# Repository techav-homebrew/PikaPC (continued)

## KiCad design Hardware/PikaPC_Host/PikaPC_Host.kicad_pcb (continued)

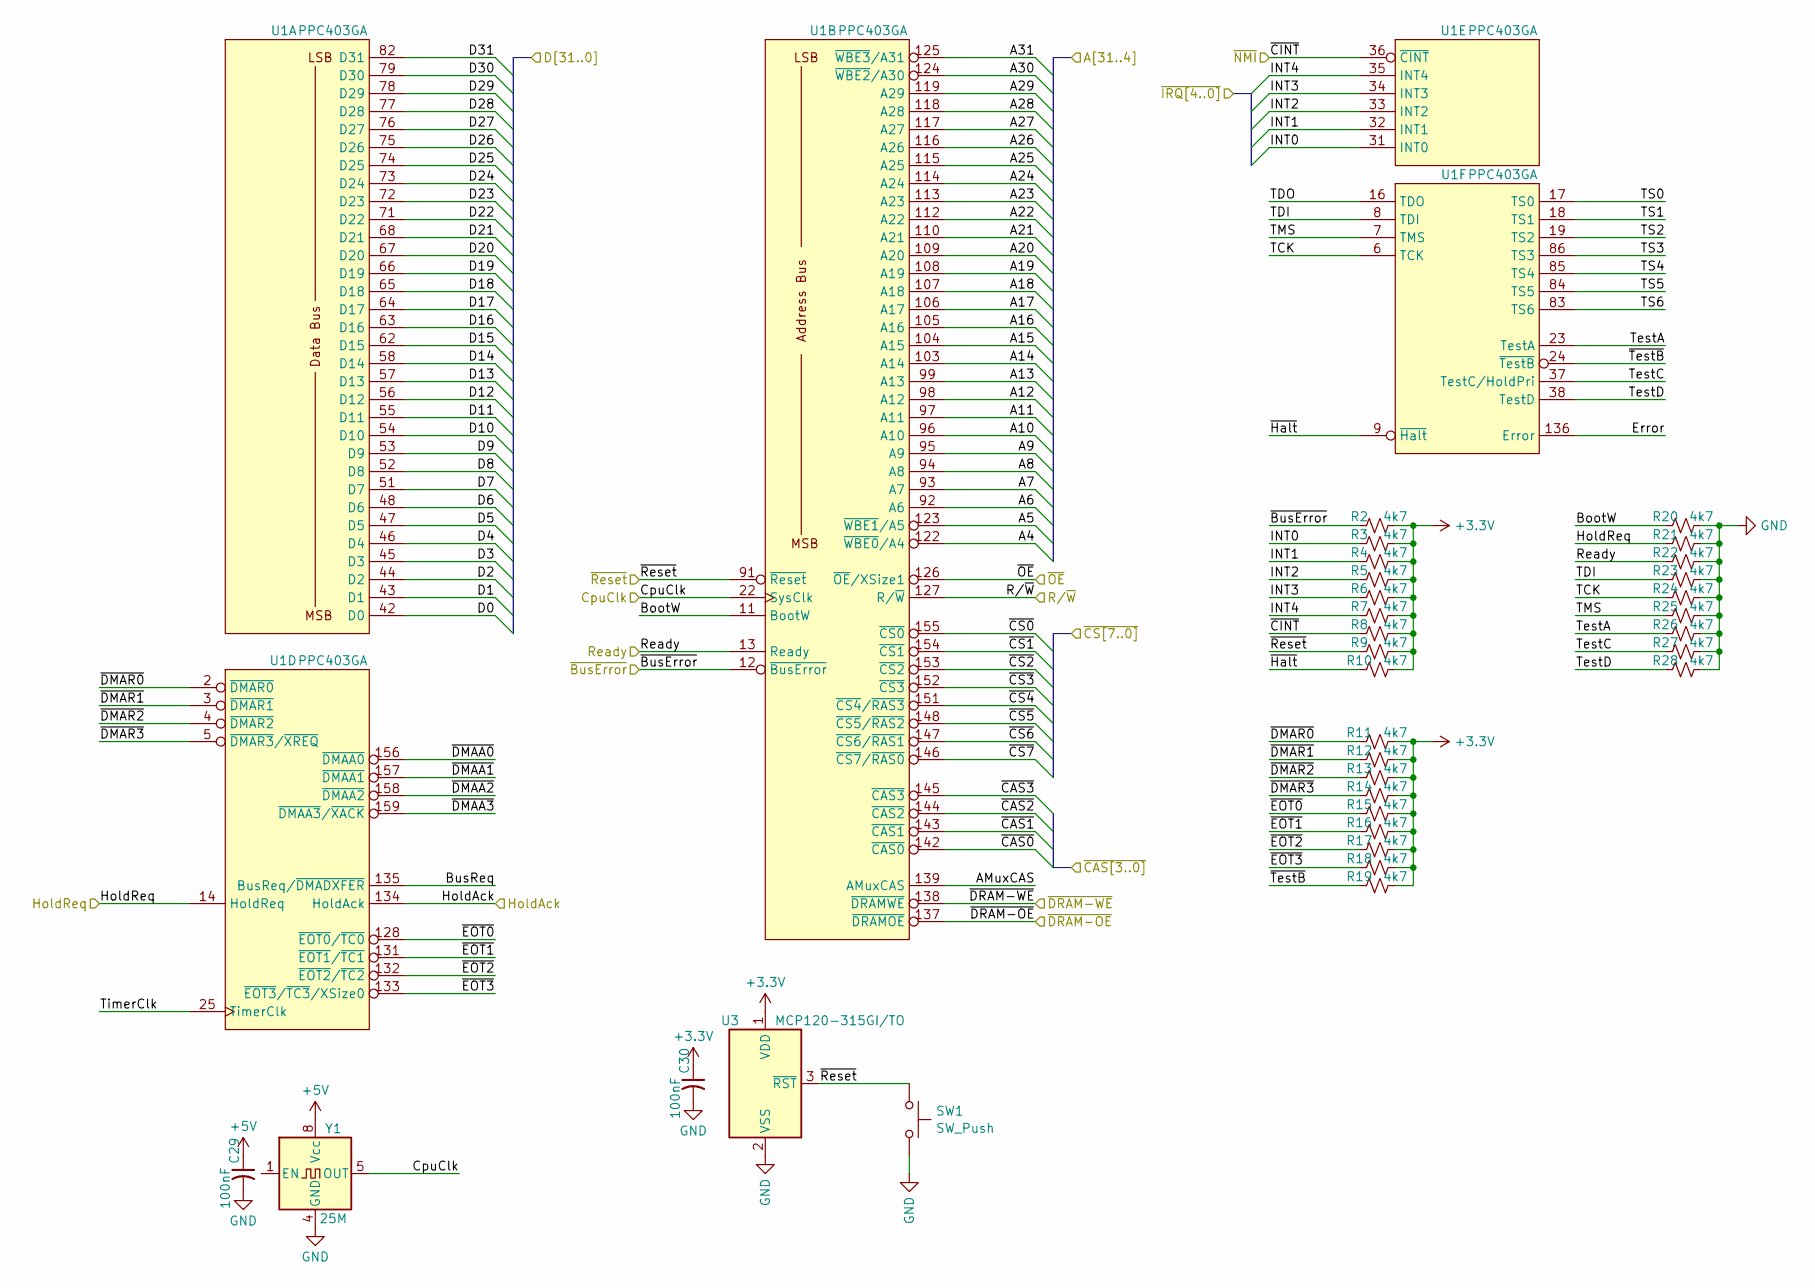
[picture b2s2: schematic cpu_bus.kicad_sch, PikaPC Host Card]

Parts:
C29, C30: 100nF; C_0805_2012Metric; Mouser 187-CL21B104KACNNNC
R2, R3, R4, R5, R6, R7, R8, R9, R10, R11, R12, R13, R14, R15, R16, R17, R18, R19, R20, R21, R22, R23, R24, R25, R26, R27, R28: 4k7; R_0805_2012Metric; Mouser 303-0805W8J0472T5E
SW1: SW_Push; SW_PUSH_6mm_H7.3mm
U1: PPC403GA; PQFP-160_28x28mm_P0.65mm
U3: MCP120-315GI/TO; TO-92_Inline_Wide; Mouser 579-MCP120-315GI/TO
Y1: 25M; Oscillator_DIP-8

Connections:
+3.3V: C30.1, R2.2, R3.2, R4.2, R5.2, R6.2, R7.2, R8.2, R9.2, R10.2, R11.2, R12.2, R13.2, R14.2, R15.2, R16.2, R17.2, R18.2, R19.2, U3.1 (VDD); also elsewhere on the board
+5V: C29.1, Y1.8 (Vcc); also elsewhere on the board
/CPU Bus/AMuxCAS: U1.139 (AMuxCAS)
/CPU Bus/BootW: R20.1, U1.11 (BootW)
/CPU Bus/BusReq: U1.135 (BusReq/~DMADXFER)
/CPU Bus/D0: U1.42 (D0); also elsewhere on the board
/CPU Bus/D1: U1.43 (D1); also elsewhere on the board
/CPU Bus/D2: U1.44 (D2); also elsewhere on the board
/CPU Bus/D3: U1.45 (D3); also elsewhere on the board
/CPU Bus/D4: U1.46 (D4); also elsewhere on the board
/CPU Bus/D5: U1.47 (D5); also elsewhere on the board
/CPU Bus/D6: U1.48 (D6); also elsewhere on the board
/CPU Bus/D7: U1.51 (D7); also elsewhere on the board
/CPU Bus/D8: U1.52 (D8); also elsewhere on the board
/CPU Bus/D9: U1.53 (D9); also elsewhere on the board
/CPU Bus/D10: U1.54 (D10); also elsewhere on the board
/CPU Bus/D11: U1.55 (D11); also elsewhere on the board
/CPU Bus/D12: U1.56 (D12); also elsewhere on the board
/CPU Bus/D13: U1.57 (D13); also elsewhere on the board
/CPU Bus/D14: U1.58 (D14); also elsewhere on the board
/CPU Bus/D15: U1.62 (D15); also elsewhere on the board
/CPU Bus/D16: U1.63 (D16); also elsewhere on the board
/CPU Bus/D17: U1.64 (D17); also elsewhere on the board
/CPU Bus/D18: U1.65 (D18); also elsewhere on the board
/CPU Bus/D19: U1.66 (D19); also elsewhere on the board
/CPU Bus/D20: U1.67 (D20); also elsewhere on the board
/CPU Bus/D21: U1.68 (D21); also elsewhere on the board
/CPU Bus/D22: U1.71 (D22); also elsewhere on the board
/CPU Bus/D23: U1.72 (D23); also elsewhere on the board
/CPU Bus/D24: U1.73 (D24); also elsewhere on the board
/CPU Bus/D25: U1.74 (D25); also elsewhere on the board
/CPU Bus/D26: U1.75 (D26); also elsewhere on the board
/CPU Bus/D27: U1.76 (D27); also elsewhere on the board
/CPU Bus/D28: U1.77 (D28); also elsewhere on the board
/CPU Bus/D29: U1.78 (D29); also elsewhere on the board
/CPU Bus/D30: U1.79 (D30); also elsewhere on the board
/CPU Bus/D31: U1.82 (D31); also elsewhere on the board
/CPU Bus/Error: U1.136 (Error)
/CPU Bus/HoldAck: U1.134 (HoldAck); also elsewhere on the board
/CPU Bus/HoldReq: R21.1, U1.14 (HoldReq); also elsewhere on the board
/CPU Bus/INT0: R3.1, U1.31 (INT0)
/CPU Bus/INT1: R4.1, U1.32 (INT1)
/CPU Bus/INT2: R5.1, U1.33 (INT2)
/CPU Bus/INT3: R6.1, U1.34 (INT3)
/CPU Bus/INT4: R7.1, U1.35 (INT4)
/CPU Bus/Ready: R22.1, U1.13 (Ready); also elsewhere on the board
/CPU Bus/TCK: R24.1, U1.6 (TCK)
/CPU Bus/TDI: R23.1, U1.8 (TDI)
/CPU Bus/TDO: U1.16 (TDO)
/CPU Bus/TMS: R25.1, U1.7 (TMS)
/CPU Bus/TS0: U1.17 (TS0)
/CPU Bus/TS1: U1.18 (TS1)
/CPU Bus/TS2: U1.19 (TS2)
/CPU Bus/TS3: U1.86 (TS3)
/CPU Bus/TS4: U1.85 (TS4)
/CPU Bus/TS5: U1.84 (TS5)
/CPU Bus/TS6: U1.83 (TS6)
/CPU Bus/TestA: R26.1, U1.23 (TestA)
/CPU Bus/TestC: R27.1, U1.37 (TestC/HoldPri)
/CPU Bus/TestD: R28.1, U1.38 (TestD)
/CPU Bus/TimerClk: U1.25 (TimerClk)
/CPU Bus/~BusError: R2.1, U1.12 (~BusError); also elsewhere on the board
/CPU Bus/~CAS0: U1.142 (~CAS0); also elsewhere on the board
/CPU Bus/~CAS1: U1.143 (~CAS1); also elsewhere on the board
/CPU Bus/~CAS2: U1.144 (~CAS2); also elsewhere on the board
/CPU Bus/~CAS3: U1.145 (~CAS3); also elsewhere on the board
/CPU Bus/~CINT: R8.1, U1.36 (~CINT); also elsewhere on the board
/CPU Bus/~CS0: U1.155 (~CS0); also elsewhere on the board
/CPU Bus/~CS1: U1.154 (~CS1); also elsewhere on the board
/CPU Bus/~CS2: U1.153 (~CS2); also elsewhere on the board
/CPU Bus/~CS3: U1.152 (~CS3); also elsewhere on the board
/CPU Bus/~CS4: U1.151 (~CS4/~RAS3); also elsewhere on the board
/CPU Bus/~CS5: U1.148 (~CS5/~RAS2); also elsewhere on the board
/CPU Bus/~CS6: U1.147 (~CS6/~RAS1); also elsewhere on the board
/CPU Bus/~CS7: U1.146 (~CS7/~RAS0); also elsewhere on the board
/CPU Bus/~DMAA0: U1.156 (~DMAA0)
/CPU Bus/~DMAA1: U1.157 (~DMAA1)
/CPU Bus/~DMAA2: U1.158 (~DMAA2)
/CPU Bus/~DMAA3: U1.159 (~DMAA3/~XACK)
/CPU Bus/~DMAR0: R11.1, U1.2 (~DMAR0)
/CPU Bus/~DMAR1: R12.1, U1.3 (~DMAR1)
/CPU Bus/~DMAR2: R13.1, U1.4 (~DMAR2)
/CPU Bus/~DMAR3: R14.1, U1.5 (~DMAR3/~XREQ)
/CPU Bus/~DRAM-OE: U1.137 (~DRAMOE); also elsewhere on the board
/CPU Bus/~DRAM-WE: U1.138 (~DRAMWE); also elsewhere on the board
/CPU Bus/~EOT0: R15.1, U1.128 (~EOT0/~TC0)
/CPU Bus/~EOT1: R16.1, U1.131 (~EOT1/~TC1)
/CPU Bus/~EOT2: R17.1, U1.132 (~EOT2/~TC2)
/CPU Bus/~EOT3: R18.1, U1.133 (~EOT3/~TC3/XSize0)
/CPU Bus/~Halt: R10.1, U1.9 (~Halt)
/CPU Bus/~OE: U1.126 (~OE/XSize1); also elsewhere on the board
/CPU Bus/~TestB: R19.1, U1.24 (~TestB)
/CpuClk: U1.22 (SysClk), Y1.5 (OUT); also elsewhere on the board
/Main Bus/A4: U1.122 (~WBE0/A4); also elsewhere on the board
/Main Bus/A5: U1.123 (~WBE1/A5); also elsewhere on the board
/Main Bus/A6: U1.92 (A6); also elsewhere on the board
/Main Bus/A7: U1.93 (A7); also elsewhere on the board
/Main Bus/A8: U1.94 (A8); also elsewhere on the board
/Main Bus/A9: U1.95 (A9); also elsewhere on the board
/Main Bus/A10: U1.96 (A10); also elsewhere on the board
/Main Bus/A11: U1.97 (A11); also elsewhere on the board
/Main Bus/A12: U1.98 (A12); also elsewhere on the board
/Main Bus/A13: U1.99 (A13); also elsewhere on the board
/Main Bus/A14: U1.103 (A14); also elsewhere on the board
/Main Bus/A15: U1.104 (A15); also elsewhere on the board
/Main Bus/A16: U1.105 (A16); also elsewhere on the board
/Main Bus/A17: U1.106 (A17); also elsewhere on the board
/Main Bus/A18: U1.107 (A18); also elsewhere on the board
/Main Bus/A19: U1.108 (A19); also elsewhere on the board
/Main Bus/A20: U1.109 (A20); also elsewhere on the board
/Main Bus/A21: U1.110 (A21); also elsewhere on the board
/Main Bus/A22: U1.112 (A22); also elsewhere on the board
/Main Bus/A23: U1.113 (A23); also elsewhere on the board
/Main Bus/A24: U1.114 (A24); also elsewhere on the board
/Main Bus/A25: U1.115 (A25); also elsewhere on the board
/Main Bus/A26: U1.116 (A26); also elsewhere on the board
/Main Bus/A27: U1.117 (A27); also elsewhere on the board
/Main Bus/A28: U1.118 (A28); also elsewhere on the board
/Main Bus/A29: U1.119 (A29); also elsewhere on the board
/Main Bus/A30: U1.124 (~WBE2/A30); also elsewhere on the board
/Main Bus/A31: U1.125 (~WBE3/A31); also elsewhere on the board
/R/~W: U1.127 (R/~W); also elsewhere on the board
/~Reset: R9.1, SW1.2, U1.91 (~Reset), U3.3 (~RST); also elsewhere on the board

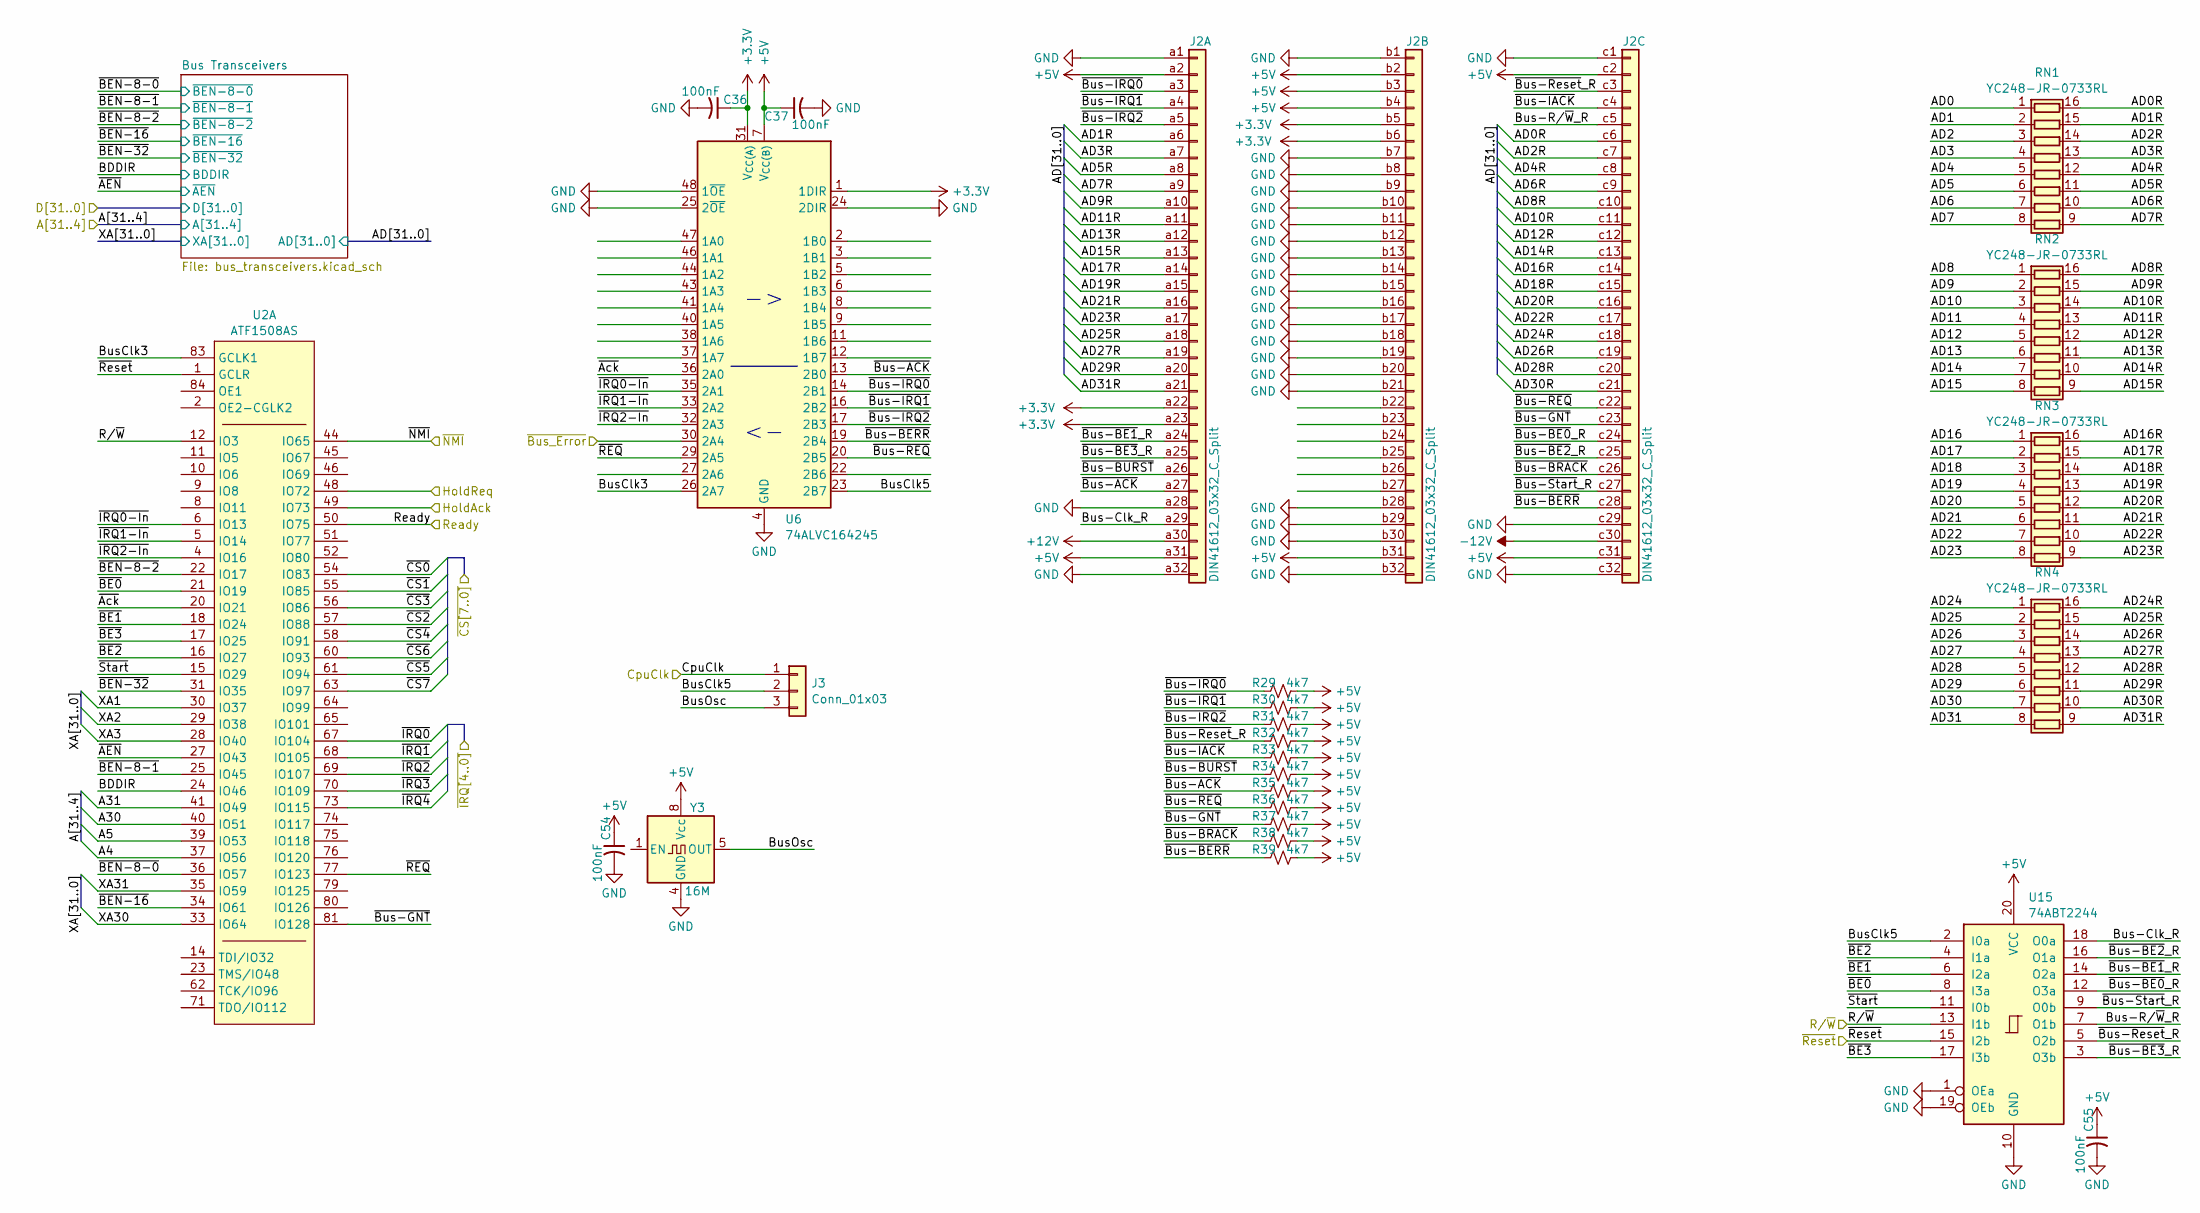
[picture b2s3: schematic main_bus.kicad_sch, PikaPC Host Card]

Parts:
C36, C37, C54, C55: 100nF; C_0805_2012Metric; Mouser 187-CL21B104KACNNNC
J2: DIN41612_03x32_C_Split; DIN41612_C_3x32_Male_Horizontal_THT
J3: Conn_01x03; PinHeader_1x03_P2.54mm_Vertical
R29, R30, R31, R32, R33, R34, R35, R36, R37, R38, R39: 4k7; R_0805_2012Metric; Mouser 303-0805W8J0472T5E
RN1, RN2, RN3, RN4: YC248-JR-0733RL; R_Array_Convex_8x0602
U2: ATF1508AS; PLCC-84_THT-Socket
U6: 74ALVC164245; TSSOP-48_6.1x12.5mm_P0.5mm; Mouser 972-74ALVC164245PAG8
U15: 74ABT2244; SOIC-20W_7.5x12.8mm_P1.27mm
Y3: 16M; Oscillator_DIP-8

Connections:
+3.3V: C36.1, J2.a22, J2.a23, J2.b5, J2.b6, U6.1 (1DIR), U6.31 (V_{CC(A)}), U6.42 (V_{CC(A)}); also elsewhere on the board
+5V: C37.1, C54.1, C55.1, J2.a2, J2.a31, J2.b2, J2.b3, J2.b4, J2.b31, J2.c2, J2.c31, R29.2, R30.2, R31.2, R32.2, R33.2, R34.2, R35.2, R36.2, R37.2, R38.2, R39.2, U6.7 (V_{CC(B)}), U6.18 (V_{CC(B)}), U15.20 (VCC), Y3.8 (Vcc); also elsewhere on the board
+12V: J2.a30; also elsewhere on the board
-12V: J2.c30; also elsewhere on the board
/CPU Bus/HoldAck: U2.49 (IO73); also elsewhere on the board
/CPU Bus/HoldReq: U2.48 (IO72); also elsewhere on the board
/CPU Bus/Ready: U2.50 (IO75); also elsewhere on the board
/CPU Bus/~BusError: U6.30 (2A4); also elsewhere on the board
/CPU Bus/~CINT: U2.44 (IO65); also elsewhere on the board
/CPU Bus/~CS0: U2.54 (IO83); also elsewhere on the board
/CPU Bus/~CS1: U2.55 (IO85); also elsewhere on the board
/CPU Bus/~CS2: U2.57 (IO88); also elsewhere on the board
/CPU Bus/~CS3: U2.56 (IO86); also elsewhere on the board
/CPU Bus/~CS4: U2.58 (IO91); also elsewhere on the board
/CPU Bus/~CS5: U2.61 (IO94); also elsewhere on the board
/CPU Bus/~CS6: U2.60 (IO93); also elsewhere on the board
/CPU Bus/~CS7: U2.63 (IO97); also elsewhere on the board
/CPU Bus/~IRQ0: U2.67 (IO104)
/CPU Bus/~IRQ1: U2.68 (IO105)
/CPU Bus/~IRQ2: U2.69 (IO107)
/CPU Bus/~IRQ3: U2.70 (IO109)
/CPU Bus/~IRQ4: U2.73 (IO115)
/CpuClk: J3.1; also elsewhere on the board
/Main Bus/A4: U2.37 (IO56); also elsewhere on the board
/Main Bus/A5: U2.39 (IO53); also elsewhere on the board
/Main Bus/A30: U2.40 (IO51); also elsewhere on the board
/Main Bus/A31: U2.41 (IO49); also elsewhere on the board
/Main Bus/AD0: RN1.1 (R1.1); also elsewhere on the board
/Main Bus/AD0R: J2.c6, RN1.16 (R1.2)
/Main Bus/AD1: RN1.2 (R2.1); also elsewhere on the board
/Main Bus/AD1R: J2.a6, RN1.15 (R2.2)
/Main Bus/AD2: RN1.3 (R3.1); also elsewhere on the board
/Main Bus/AD2R: J2.c7, RN1.14 (R3.2)
/Main Bus/AD3: RN1.4 (R4.1); also elsewhere on the board
/Main Bus/AD3R: J2.a7, RN1.13 (R4.2)
/Main Bus/AD4: RN1.5 (R5.1); also elsewhere on the board
/Main Bus/AD4R: J2.c8, RN1.12 (R5.2)
/Main Bus/AD5: RN1.6 (R6.1); also elsewhere on the board
/Main Bus/AD5R: J2.a8, RN1.11 (R6.2)
/Main Bus/AD6: RN1.7 (R7.1); also elsewhere on the board
/Main Bus/AD6R: J2.c9, RN1.10 (R7.2)
/Main Bus/AD7: RN1.8 (R8.1); also elsewhere on the board
/Main Bus/AD7R: J2.a9, RN1.9 (R8.2)
/Main Bus/AD8: RN2.1 (R1.1); also elsewhere on the board
/Main Bus/AD8R: J2.c10, RN2.16 (R1.2)
/Main Bus/AD9: RN2.2 (R2.1); also elsewhere on the board
/Main Bus/AD9R: J2.a10, RN2.15 (R2.2)
/Main Bus/AD10: RN2.3 (R3.1); also elsewhere on the board
/Main Bus/AD10R: J2.c11, RN2.14 (R3.2)
/Main Bus/AD11: RN2.4 (R4.1); also elsewhere on the board
/Main Bus/AD11R: J2.a11, RN2.13 (R4.2)
/Main Bus/AD12: RN2.5 (R5.1); also elsewhere on the board
/Main Bus/AD12R: J2.c12, RN2.12 (R5.2)
/Main Bus/AD13: RN2.6 (R6.1); also elsewhere on the board
/Main Bus/AD13R: J2.a12, RN2.11 (R6.2)
/Main Bus/AD14: RN2.7 (R7.1); also elsewhere on the board
/Main Bus/AD14R: J2.c13, RN2.10 (R7.2)
/Main Bus/AD15: RN2.8 (R8.1); also elsewhere on the board
/Main Bus/AD15R: J2.a13, RN2.9 (R8.2)
/Main Bus/AD16: RN3.1 (R1.1); also elsewhere on the board
/Main Bus/AD16R: J2.c14, RN3.16 (R1.2)
/Main Bus/AD17: RN3.2 (R2.1); also elsewhere on the board
/Main Bus/AD17R: J2.a14, RN3.15 (R2.2)
/Main Bus/AD18: RN3.3 (R3.1); also elsewhere on the board
/Main Bus/AD18R: J2.c15, RN3.14 (R3.2)
/Main Bus/AD19: RN3.4 (R4.1); also elsewhere on the board
/Main Bus/AD19R: J2.a15, RN3.13 (R4.2)
/Main Bus/AD20: RN3.5 (R5.1); also elsewhere on the board
/Main Bus/AD20R: J2.c16, RN3.12 (R5.2)
/Main Bus/AD21: RN3.6 (R6.1); also elsewhere on the board
/Main Bus/AD21R: J2.a16, RN3.11 (R6.2)
/Main Bus/AD22: RN3.7 (R7.1); also elsewhere on the board
/Main Bus/AD22R: J2.c17, RN3.10 (R7.2)
/Main Bus/AD23: RN3.8 (R8.1); also elsewhere on the board
/Main Bus/AD23R: J2.a17, RN3.9 (R8.2)
/Main Bus/AD24: RN4.1 (R1.1); also elsewhere on the board
/Main Bus/AD24R: J2.c18, RN4.16 (R1.2)
/Main Bus/AD25: RN4.2 (R2.1); also elsewhere on the board
/Main Bus/AD25R: J2.a18, RN4.15 (R2.2)
/Main Bus/AD26: RN4.3 (R3.1); also elsewhere on the board
/Main Bus/AD26R: J2.c19, RN4.14 (R3.2)
/Main Bus/AD27: RN4.4 (R4.1); also elsewhere on the board
/Main Bus/AD27R: J2.a19, RN4.13 (R4.2)
/Main Bus/AD28: RN4.5 (R5.1); also elsewhere on the board
/Main Bus/AD28R: J2.c20, RN4.12 (R5.2)
/Main Bus/AD29: RN4.6 (R6.1); also elsewhere on the board
/Main Bus/AD29R: J2.a20, RN4.11 (R6.2)
/Main Bus/AD30: RN4.7 (R7.1); also elsewhere on the board
/Main Bus/AD30R: J2.c21, RN4.10 (R7.2)
/Main Bus/AD31: RN4.8 (R8.1); also elsewhere on the board
/Main Bus/AD31R: J2.a21, RN4.9 (R8.2)
/Main Bus/BDDIR: U2.24 (IO46); also elsewhere on the board
/Main Bus/Bus-Clk_R: J2.a29, U15.18 (O0a)
/Main Bus/Bus-R/~W_R: J2.c5, U15.7 (O1b)
/Main Bus/BusClk3: U2.83 (GCLK1), U6.26 (2A7)
/Main Bus/BusClk5: J3.2, U6.23 (2B7), U15.2 (I0a)
/Main Bus/BusOsc: J3.3, Y3.5 (OUT)
/Main Bus/XA1: U2.30 (IO37); also elsewhere on the board
/Main Bus/XA2: U2.29 (IO38); also elsewhere on the board
/Main Bus/XA3: U2.28 (IO40); also elsewhere on the board
/Main Bus/XA30: U2.33 (IO64); also elsewhere on the board
/Main Bus/XA31: U2.35 (IO59); also elsewhere on the board
/Main Bus/~AEN: U2.27 (IO43); also elsewhere on the board
/Main Bus/~Ack: U2.20 (IO21), U6.36 (2A0)
/Main Bus/~BE0: U2.21 (IO19), U15.8 (I3a)
/Main Bus/~BE1: U2.18 (IO24), U15.6 (I2a)
/Main Bus/~BE2: U2.16 (IO27), U15.4 (I1a)
/Main Bus/~BE3: U2.17 (IO25), U15.17 (I3b)
/Main Bus/~BEN-8-0: U2.36 (IO57); also elsewhere on the board
/Main Bus/~BEN-8-1: U2.25 (IO45); also elsewhere on the board
/Main Bus/~BEN-8-2: U2.22 (IO17); also elsewhere on the board
/Main Bus/~BEN-16: U2.34 (IO61); also elsewhere on the board
/Main Bus/~BEN-32: U2.31 (IO35); also elsewhere on the board
/Main Bus/~Bus-ACK: J2.a27, R35.1, U6.13 (2B0)
/Main Bus/~Bus-BE0_R: J2.c24, U15.12 (O3a)
/Main Bus/~Bus-BE1_R: J2.a24, U15.14 (O2a)
/Main Bus/~Bus-BE2_R: J2.c25, U15.16 (O1a)
/Main Bus/~Bus-BE3_R: J2.a25, U15.3 (O3b)
/Main Bus/~Bus-BERR: J2.c28, R39.1, U6.19 (2B4)
/Main Bus/~Bus-BRACK: J2.c26, R38.1
/Main Bus/~Bus-BURST: J2.a26, R34.1
/Main Bus/~Bus-GNT: J2.c23, R37.1, U2.81 (IO128)
/Main Bus/~Bus-IACK: J2.c4, R33.1
/Main Bus/~Bus-IRQ0: J2.a3, R29.1, U6.14 (2B1)
/Main Bus/~Bus-IRQ1: J2.a4, R30.1, U6.16 (2B2)
/Main Bus/~Bus-IRQ2: J2.a5, R31.1, U6.17 (2B3)
/Main Bus/~Bus-REQ: J2.c22, R36.1, U6.20 (2B5)
/Main Bus/~Bus-Reset_R: J2.c3, R32.1, U15.5 (O2b)
/Main Bus/~Bus-Start_R: J2.c27, U15.9 (O0b)
/Main Bus/~IRQ0-In: U2.6 (IO13), U6.35 (2A1)
/Main Bus/~IRQ1-In: U2.5 (IO14), U6.33 (2A2)
/Main Bus/~IRQ2-In: U2.4 (IO16), U6.32 (2A3)
/Main Bus/~REQ: U2.77 (IO123), U6.29 (2A5)
/Main Bus/~Start: U2.15 (IO29), U15.11 (I0b)
/R/~W: U2.12 (IO3), U15.13 (I1b); also elsewhere on the board
/~Reset: U2.1 (GCLR), U15.15 (I2b); also elsewhere on the board

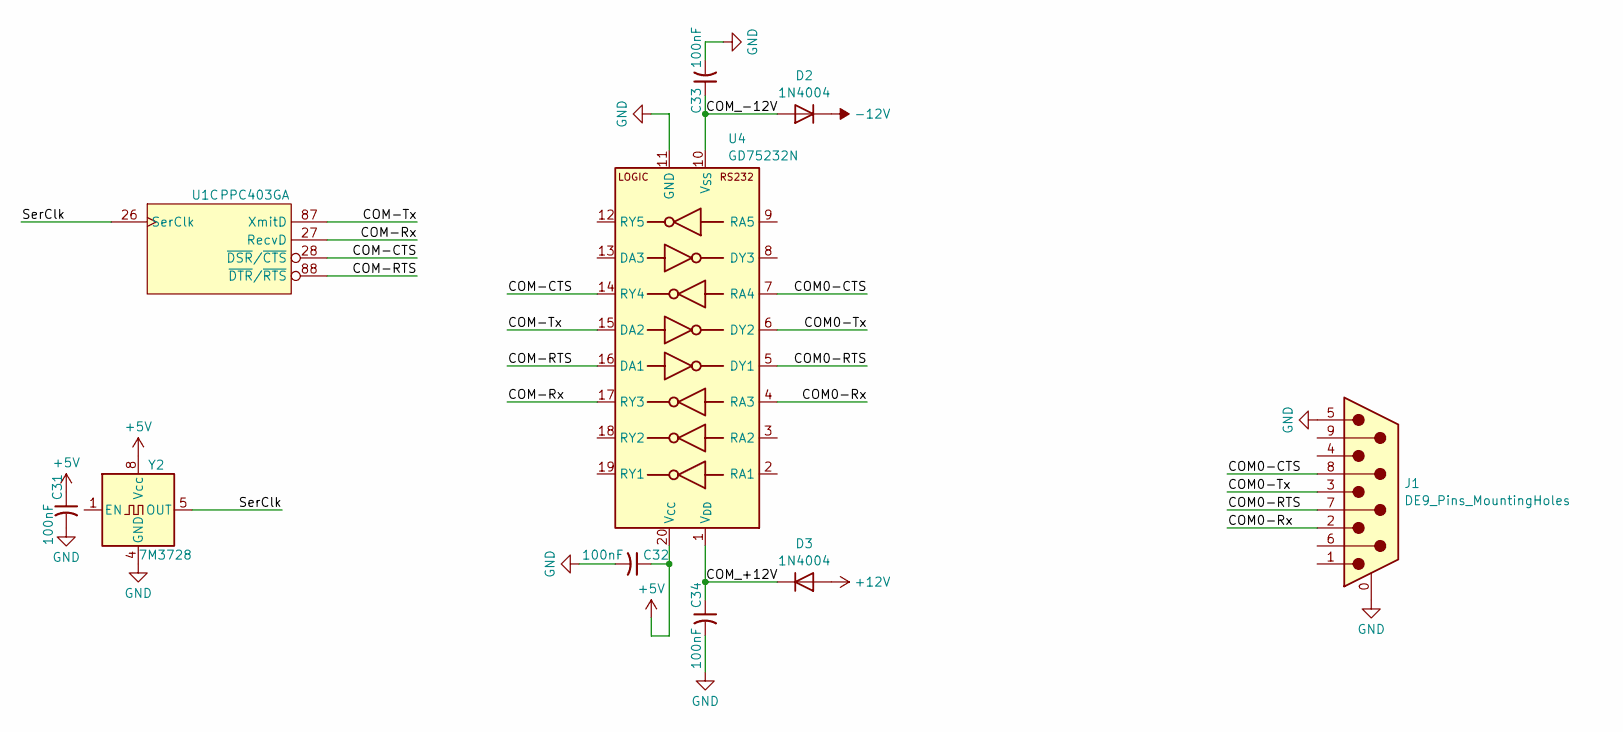
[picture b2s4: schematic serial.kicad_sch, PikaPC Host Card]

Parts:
C31, C32, C33, C34: 100nF; C_0805_2012Metric; Mouser 187-CL21B104KACNNNC
D2, D3: 1N4004; D_DO-41_SOD81_P7.62mm_Horizontal; Mouser 750-1N4004-G
J1: DE9_Pins_MountingHoles; DSUB-9_Pins_Horizontal_P2.77x2.84mm_EdgePinOffset4.94mm_Hou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
U1: PPC403GA; PQFP-160_28x28mm_P0.65mm
U4: GD75232N; DIP-20_W7.62mm; Mouser 595-GD75232N
Y2: 7M3728; Oscillator_DIP-8

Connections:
+5V: C31.1, C32.1, U4.20 (V_{CC}), Y2.8 (Vcc); also elsewhere on the board
+12V: D3.2 (A); also elsewhere on the board
-12V: D2.1 (K); also elsewhere on the board
/Serial/COM0-CTS: J1.8, U4.7 (RA4)
/Serial/COM0-RTS: J1.7, U4.5 (DY1)
/Serial/COM0-Rx: J1.2, U4.4 (RA3)
/Serial/COM0-Tx: J1.3, U4.6 (DY2)
/Serial/COM-CTS: U1.28 (~DSR/~CTS), U4.14 (RY4)
/Serial/COM-RTS: U1.88 (~DTR/~RTS), U4.16 (DA1)
/Serial/COM-Rx: U1.27 (RecvD), U4.17 (RY3)
/Serial/COM-Tx: U1.87 (XmitD), U4.15 (DA2)
/Serial/COM_+12V: C34.1, D3.1 (K), U4.1 (V_{DD})
/Serial/COM_-12V: C33.1, D2.2 (A), U4.10 (V_{SS})
/Serial/SerClk: U1.26 (SerClk), Y2.5 (OUT)

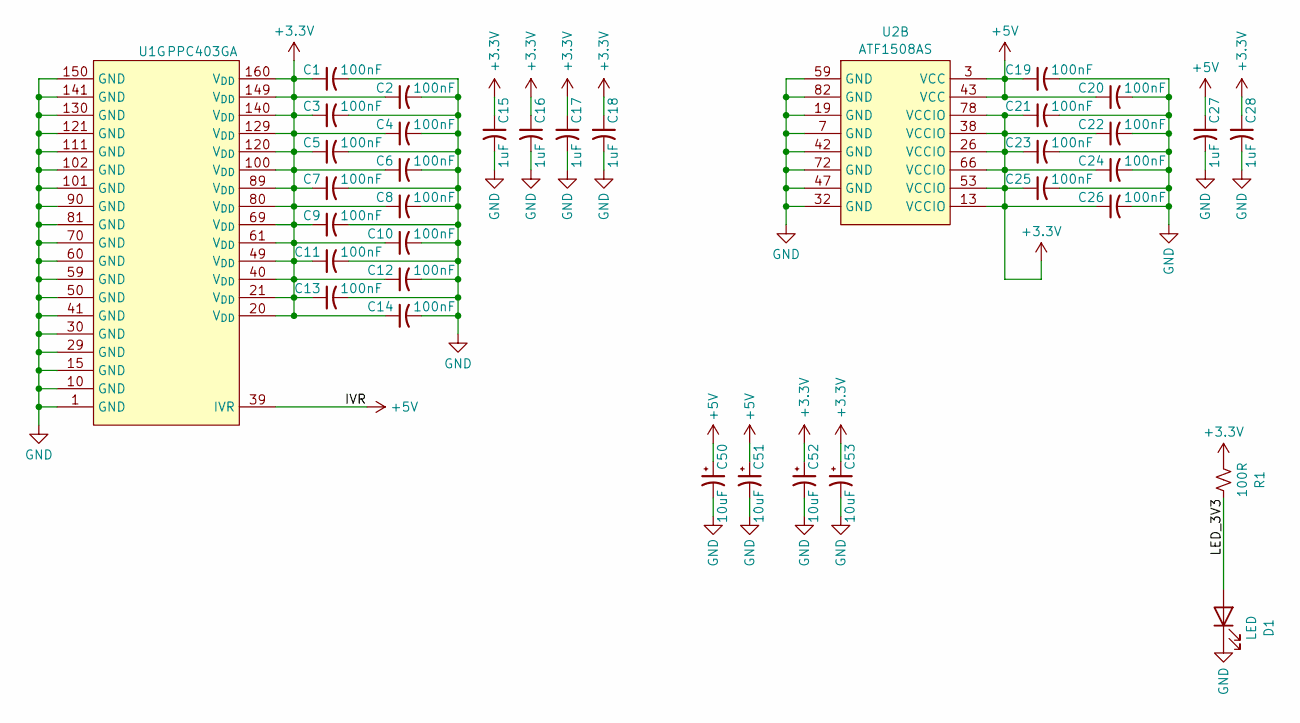
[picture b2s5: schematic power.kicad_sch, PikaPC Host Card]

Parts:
C1, C2, C3, C4, C5, C6, C7, C8, C9, C10, C11, C12, C13, C14, C19, C20, C21, C22, C23, C24, C25, C26: 100nF; C_0805_2012Metric; Mouser 187-CL21B104KACNNNC
C15, C16, C17, C18, C27, C28: 1uF; C_0805_2012Metric; Mouser 187-CL21B105KOFNNNG
C50, C51, C52, C53: 10uF; CP_Elec_4x5.7; Mouser 80-EDK106M016A9BAA
D1: LED; LED_D5.0mm_Horizontal_O3.81mm_Z3.0mm
R1: 100R; R_0805_2012Metric
U1: PPC403GA; PQFP-160_28x28mm_P0.65mm
U2: ATF1508AS; PLCC-84_THT-Socket

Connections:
+3.3V: C1.1, C2.1, C3.1, C4.1, C5.1, C6.1, C7.1, C8.1, C9.1, C10.1, C11.1, C12.1, C13.1, C14.1, C15.1, C16.1, C17.1, C18.1, C21.1, C22.1, C23.1, C24.1, C25.1, C26.1, C28.1, C52.1, C53.1, R1.1, U1.20 (V_{DD}), U1.21 (V_{DD}), U1.40 (V_{DD}), U1.49 (V_{DD}), U1.61 (V_{DD}), U1.69 (V_{DD}), U1.80 (V_{DD}), U1.89 (V_{DD}), U1.100 (V_{DD}), U1.120 (V_{DD}), U1.129 (V_{DD}), U1.140 (V_{DD}), U1.149 (V_{DD}), U1.160 (V_{DD}), U2.13 (VCCIO), U2.26 (VCCIO), U2.38 (VCCIO), U2.53 (VCCIO), U2.66 (VCCIO), U2.78 (VCCIO); also elsewhere on the board
+5V: C19.1, C20.1, C27.1, C50.1, C51.1, U1.39 (IVR), U2.3 (VCC), U2.43 (VCC); also elsewhere on the board
/Power/LED_3V3: D1.2 (A), R1.2
